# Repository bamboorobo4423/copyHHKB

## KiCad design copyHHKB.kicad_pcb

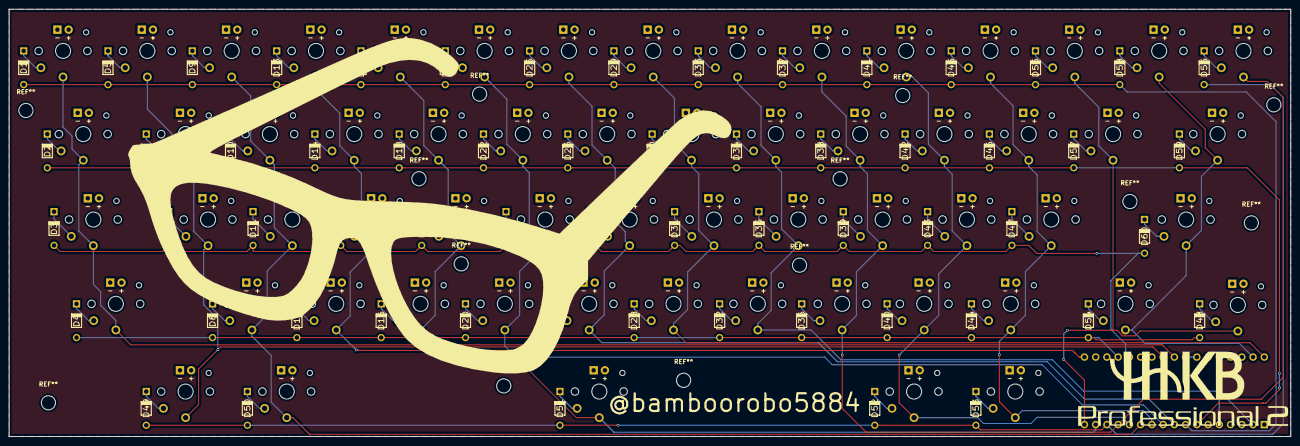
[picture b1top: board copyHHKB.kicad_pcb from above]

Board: 2 copper layers, 289.6 x 96.5 mm, 121 parts (1 on the bottom side), 79 nets.

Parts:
!1: SW_DIP_x01; Kailh-PG1350-1u
$1: SW_DIP_x01; Kailh-PG1350-1u
%1: SW_DIP_x01; Kailh-PG1350-1u
&1: SW_DIP_x01; Kailh-PG1350-1u
'1: SW_DIP_x01; Kailh-PG1350-1u
(1: SW_DIP_x01; Kailh-PG1350-1u
)1: SW_DIP_x01; Kailh-PG1350-1u
*1: SW_DIP_x01; Kailh-PG1350-1u
+1: SW_DIP_x01; Kailh-PG1350-1u
/1: SW_DIP_x01; Kailh-PG1350-1u
;1: SW_DIP_x01; Kailh-PG1350-1u
<1: SW_DIP_x01; Kailh-PG1350-1u
>1: SW_DIP_x01; Kailh-PG1350-1u
@1: SW_DIP_x01; Kailh-PG1350-1u
AltL1: SW_DIP_x01; Kailh-PG1350-1u
AltR1: SW_DIP_x01; Kailh-PG1350-1u
BackSP1: SW_DIP_x01; Kailh-PG1350-1u
Control1: SW_DIP_x01; Kailh-PG1350-1u
D1, D2, D3, D4, D5, D6, D7, D8, D9, D10, D11, D12, D13, D14, D15, D16, D17, D18, D19, D20, D21, D22, D23, D24, D25, D26, D27, D28, D29, D30, D31, D32, D33, D34, D35, D36, D37, D38, D39, D40, D41, D42, D43, D44, D45, D46, D47, D48, D49, D50, D51, D52, D53, D54, D55, D56, D57, D58, D59, D60: D; Diode
ESC1: SW_DIP_x01; Kailh-PG1350-1u
Enter1: SW_DIP_x01; Kailh-PG1350-1u
Fn1: SW_DIP_x01; Kailh-PG1350-1u
L1: SW_DIP_x01; Kailh-PG1350-1u
SP1: SW_DIP_x01; Kailh-PG1350-1u
U1: ARDUINO_MICRO_SHIELD
[1: SW_DIP_x01; Kailh-PG1350-1u
]1: SW_DIP_x01; Kailh-PG1350-1u
^1: SW_DIP_x01; Kailh-PG1350-1u
_1: SW_DIP_x01; Kailh-PG1350-1u
`1: SW_DIP_x01; Kailh-PG1350-1u
a1, a3: SW_DIP_x01; Kailh-PG1350-1u
b1: SW_DIP_x01; Kailh-PG1350-1u
c1: SW_DIP_x01; Kailh-PG1350-1u
d1: SW_DIP_x01; Kailh-PG1350-1u
e1: SW_DIP_x01; Kailh-PG1350-1u
f1: SW_DIP_x01; Kailh-PG1350-1u
g1: SW_DIP_x01; Kailh-PG1350-1u
h1: SW_DIP_x01; Kailh-PG1350-1u
i1: SW_DIP_x01; Kailh-PG1350-1u
j1: SW_DIP_x01; Kailh-PG1350-1u
k1: SW_DIP_x01; Kailh-PG1350-1u
m1: SW_DIP_x01; Kailh-PG1350-1u
n1: SW_DIP_x01; Kailh-PG1350-1u
o1: SW_DIP_x01; Kailh-PG1350-1u
p1: SW_DIP_x01; Kailh-PG1350-1u
q1: SW_DIP_x01; Kailh-PG1350-1u
r1: SW_DIP_x01; Kailh-PG1350-1u
s1: SW_DIP_x01; Kailh-PG1350-1u
shiftL1: SW_DIP_x01; Kailh-PG1350-1u
shiftR1: SW_DIP_x01; Kailh-PG1350-1u
t1: SW_DIP_x01; Kailh-PG1350-1u
tab1: SW_DIP_x01; Kailh-PG1350-1u
u1: SW_DIP_x01; Kailh-PG1350-1u
v1: SW_DIP_x01; Kailh-PG1350-1u
w1: SW_DIP_x01; Kailh-PG1350-1u
winL1: SW_DIP_x01; Kailh-PG1350-1u
winR1: SW_DIP_x01; Kailh-PG1350-1u
x1: SW_DIP_x01; Kailh-PG1350-1u
y1: SW_DIP_x01; Kailh-PG1350-1u
z1: SW_DIP_x01; Kailh-PG1350-1u
|1: SW_DIP_x01; Kailh-PG1350-1u

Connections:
unnamed: !1.2, D5.2
unnamed: $1.2, D17.2
unnamed: %1.2, D21.2
unnamed: &1.2, D29.2
unnamed: '1.2, D47.2
unnamed: (1.2, D37.2
unnamed: )1.2, D41.2
unnamed: *1.2, D33.2
unnamed: +1.2, D56.2
unnamed: /1.2, D44.2
unnamed: ;1.2, D43.2
unnamed: <1.2, D36.2
unnamed: >1.2, D40.2
unnamed: @1.2, D9.2
unnamed: AltL1.2, D49.2
unnamed: AltR1.2, D53.2
unnamed: BackSP1.2, D59.2
unnamed: Control1.2, D3.2
unnamed: D1.2, ESC1.2
unnamed: D2.2, tab1.2
unnamed: D4.2, shiftL1.2
unnamed: D6.2, q1.2
unnamed: D7.2, a1.2
unnamed: D8.2, z1.2
unnamed: D10.2, w1.2
unnamed: D11.2, s1.2
unnamed: D12.2, x1.2
unnamed: D13.2, a3.2
unnamed: D14.2, e1.2
unnamed: D15.2, d1.2
unnamed: D16.2, c1.2
unnamed: D18.2, r1.2
unnamed: D19.2, f1.2
unnamed: D20.2, v1.2
unnamed: D22.2, t1.2
unnamed: D23.2, g1.2
unnamed: D24.2, b1.2
unnamed: D25.2, ^1.2
unnamed: D26.2, y1.2
unnamed: D27.2, h1.2
unnamed: D28.2, n1.2
unnamed: D30.2, u1.2
unnamed: D31.2, j1.2
unnamed: D32.2, m1.2
unnamed: D34.2, i1.2
unnamed: D35.2, k1.2
unnamed: D38.2, o1.2
unnamed: D39.2, L1.2
unnamed: D42.2, p1.2
unnamed: D45.2, _1.2
unnamed: D46.2, [1.2
unnamed: D48.2, Fn1.2
unnamed: D50.2, winL1.2
unnamed: D51.2, SP1.2
unnamed: D52.2, winR1.2
unnamed: D54.2, shiftR1.2
unnamed: D55.2, `1.2
unnamed: D57.2, ]1.2
unnamed: D58.2, |1.2
unnamed: D60.2, Enter1.2
col0: Control1.1, ESC1.1, U1.A5, shiftL1.1, tab1.1
col1: !1.1, AltL1.1, U1.A4, a1.1, q1.1
col2: @1.1, U1.7, s1.1, w1.1, winL1.1, z1.1
col3: U1.13, a3.1, d1.1, e1.1, x1.1
col4: $1.1, U1.5, c1.1, f1.1, r1.1
col5: %1.1, SP1.1, U1.11, g1.1, t1.1, v1.1
col6: U1.4, ^1.1, b1.1, h1.1, y1.1
col7: &1.1, U1.SCK, j1.1, n1.1, u1.1
col8: *1.1, U1.SS, i1.1, k1.1, m1.1
col9: (1.1, <1.1, L1.1, U1.9, `1.1, o1.1
col10: )1.1, ;1.1, >1.1, U1.8, p1.1, winR1.1
col11: '1.1, /1.1, AltR1.1, U1.6, [1.1, _1.1
col12: +1.1, Fn1.1, U1.12, ]1.1
col13: BackSP1.1, Enter1.1, U1.MI, shiftR1.1, |1.1
row0: D1.1, D5.1, D9.1, D13.1, D17.1, D21.1, D25.1, D29.1, D33.1, D37.1, D41.1, D45.1, D56.1, D58.1, U1.3
row1: D2.1, D6.1, D10.1, D14.1, D18.1, D22.1, D26.1, D30.1, D34.1, D38.1, D42.1, D46.1, D57.1, D59.1, U1.2
row2: D3.1, D7.1, D11.1, D15.1, D19.1, D23.1, D27.1, D31.1, D35.1, D39.1, D43.1, D47.1, D60.1, U1.A1
row3: D4.1, D8.1, D12.1, D16.1, D20.1, D24.1, D28.1, D32.1, D36.1, D40.1, D44.1, D48.1, D54.1, U1.A0
row4: D49.1, D50.1, D51.1, D52.1, D53.1, D55.1, U1.10

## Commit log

2018-06-16 いろいろ直してる
    キーの名前をつけてる
2018-06-16 回路図のSwitchにすべてのキーをワイフッタ
2018-07-03 まーいろいろ
    ベースにするキーボードの選定し直し
2018-07-03 とりあえず配線図は完成
    ちるだの位置が結構ひどい位置にあったな
2018-07-03 pro microのピンの割り振り
    C6ぐらいまでつけた
2018-07-04 あ
    とりあえず回路図はできたかな
2018-07-04 実体配線図を考え始めた
    実体配線図を考え始めた
2018-08-09 割と実際のサイズを計算してスイッチを着始めた
    0.05mm大きいけど気にしない方向性
2018-08-10 とりあえず動くレベル
2018-08-14 配線の修正
    いいかんじになったかな
2018-08-14 logoとか追加
2018-08-15 色々問題発覚したのでそれの修正
    microのPINとスイッチが干渉してたので
    microの位置を右下に変更
2018-08-16 とりあえず発注した
